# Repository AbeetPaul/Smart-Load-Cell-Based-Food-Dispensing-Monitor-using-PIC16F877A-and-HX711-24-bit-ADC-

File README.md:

# Smart Food Dispensing Monitor: PIC16F877A + HX711

A custom KiCad-designed PCB for precise weight measurement in food dispensing management. The board pairs a PIC16F877A microcontroller with the HX711 24-bit ADC to acquire load cell data using assembly firmware.

## Repository Structure

```
/fabrication    → Primary manufacturing files (e.g., 1st.kicad_sch)
/documentation  → High-resolution PCB layouts and circuit schematics
/firmware       → Assembly source (.asm) and compiled .HEX file
```

## Hardware Architecture

The system combines the versatile PIC family with the 24-bit precision needed for sensitive load cell data acquisition, a balanced and cost-effective solution.

| Component | Specification | Role |
|-----------|---------------|------|
| U1 | PIC16F877A-IP | Central processing unit; runs the assembly logic and manages data flow |
| U2 | HX711 | 24-bit ADC designed for load cell and bridge sensor interfacing |
| Y1 | 4 MHz Crystal | Primary clock source; gives a 1 µs instruction cycle (Fosc/4) |
| R1 | 10k Resistor | Pull-up on MCLR (Pin 1) to prevent accidental resets |
| C1, C2 | 22 pF Capacitors | Stabilize the crystal oscillator for clean clock generation |

### Pin Connections

| PIC16F877A | HX711 | Configuration |
|------------|-------|---------------|
| RB0 (Pin 33) | DOUT (Pin 12) | Input: detects data-ready and receives the serial bitstream |
| RB1 (Pin 34) | PD_SCK (Pin 11) | Output: drives the serial clock and power-down control |

## Firmware Logic

The firmware follows a four-stage communication protocol:

1. **Data-ready polling:** monitors the HX711 using `BTFSC` on `PORTB,0` and waits for DOUT to go low, signaling a completed conversion.
2. **24-bit retrieval:** performs three successive 8-bit reads into `DATA_H` (high), `DATA_M` (middle), and `DATA_L` (low) to rebuild the full 24-bit raw value.
3. **Gain selection:** after the 24th bit, applies a 25th clock pulse by toggling RB1 high then low, setting gain to 128 on Channel A for the next conversion.
4. **Output mapping:** sends `DATA_L` to PORTC (Pins 15-18 and 23-26) for external monitoring, debugging, or immediate processing.

### Timing Note

The 4 MHz oscillator gives a standard 1 µs instruction cycle. The current `DELAY_500MS` loop constants (200 and 250) produce an actual delay of about **250 ms**. If you need a strict 500 ms update rate, adjust these constants.

## Simulation and Deployment

The schematic and PCB layout were developed in KiCad EDA. Verifying the firmware in simulation before building hardware reduces the risk of failure.

### Virtual Simulation
1. Open Proteus or SimulIDE.
2. Load the compiled `.HEX` file from `/firmware` into the virtual PIC16F877A.
3. Monitor the bit-banging sequence on RB0 and RB1 to verify the communication logic and the gain selection pulse.

### Physical Programming
The PCB includes an **ICSP header (J1)**, so the PIC16F877A can be flashed directly on the board. This allows quick firmware updates and final calibration without removing the chip.

## Tech Stack

`PIC16F877A` · `HX711` · `KiCad` · `PIC Assembly` · `Proteus / SimulIDE`

# MindMap

# Final PCB Design

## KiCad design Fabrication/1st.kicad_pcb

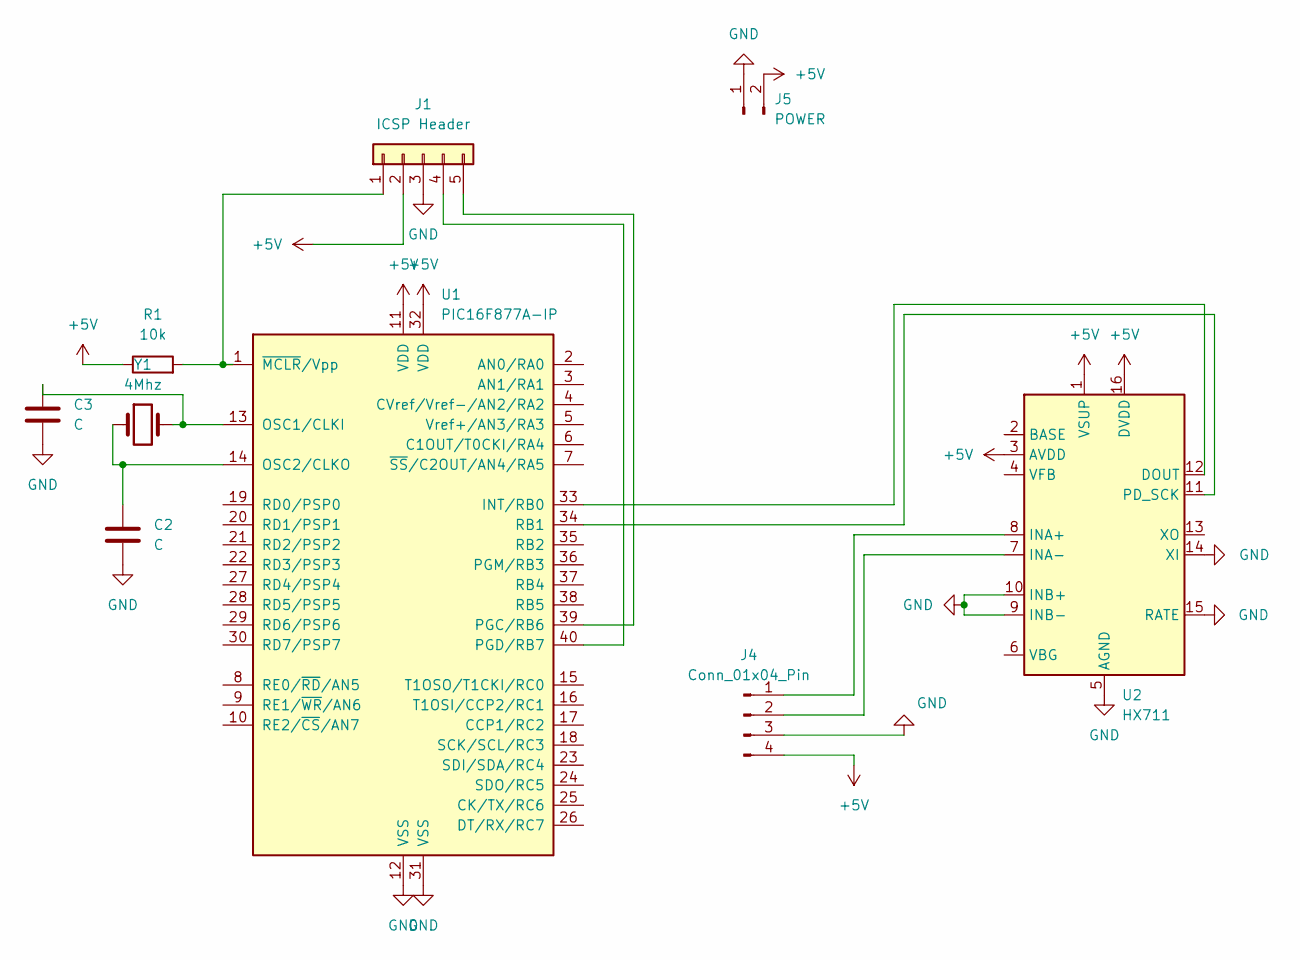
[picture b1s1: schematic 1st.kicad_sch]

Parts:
C2, C3: C; C_Disc_D5.0mm_W2.5mm_P5.00mm
J1: ICSP Header; PinHeader_1x05_P2.54mm_Vertical
J4: Conn_01x04_Pin; PinHeader_1x04_P2.54mm_Vertical
J5: POWER; PinHeader_1x02_P2.54mm_Vertical
R1: 10k; R_Axial_DIN0207_L6.3mm_D2.5mm_P10.16mm_Horizontal
U1: PIC16F877A-IP; DIP-40_W15.24mm
U2: HX711; SOIC-16_3.9x9.9mm_P1.27mm
Y1: 4Mhz; Crystal_HC49-U_Vertical

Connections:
+5V: J1.2, J4.4 (+5V), J5.2, R1.1, U1.11 (VDD), U1.32 (VDD), U2.1 (VSUP), U2.3 (AVDD), U2.16 (DVDD)
GND: C2.2, C3.2, J1.3, J4.3 (GND), J5.1, U1.12 (VSS), U1.31 (VSS), U2.5 (AGND), U2.9 (INB-), U2.10 (INB+), U2.14 (XI), U2.15 (RATE)
unnamed: J1.1, R1.2, U1.1 (~MCLR/Vpp)
unnamed: J1.4, U1.40 (PGD/RB7)
unnamed: J1.5, U1.39 (PGC/RB6)
unnamed: J4.1 (A+), U2.8 (INA+)
unnamed: J4.2 (A-), U2.7 (INA-)
unnamed: U1.33 (INT/RB0), U2.12 (DOUT)
unnamed: C3.1, U1.13 (OSC1/CLKI), Y1.2
unnamed: C2.1, U1.14 (OSC2/CLKO), Y1.1
unnamed: U1.34 (RB1), U2.11 (PD_SCK)

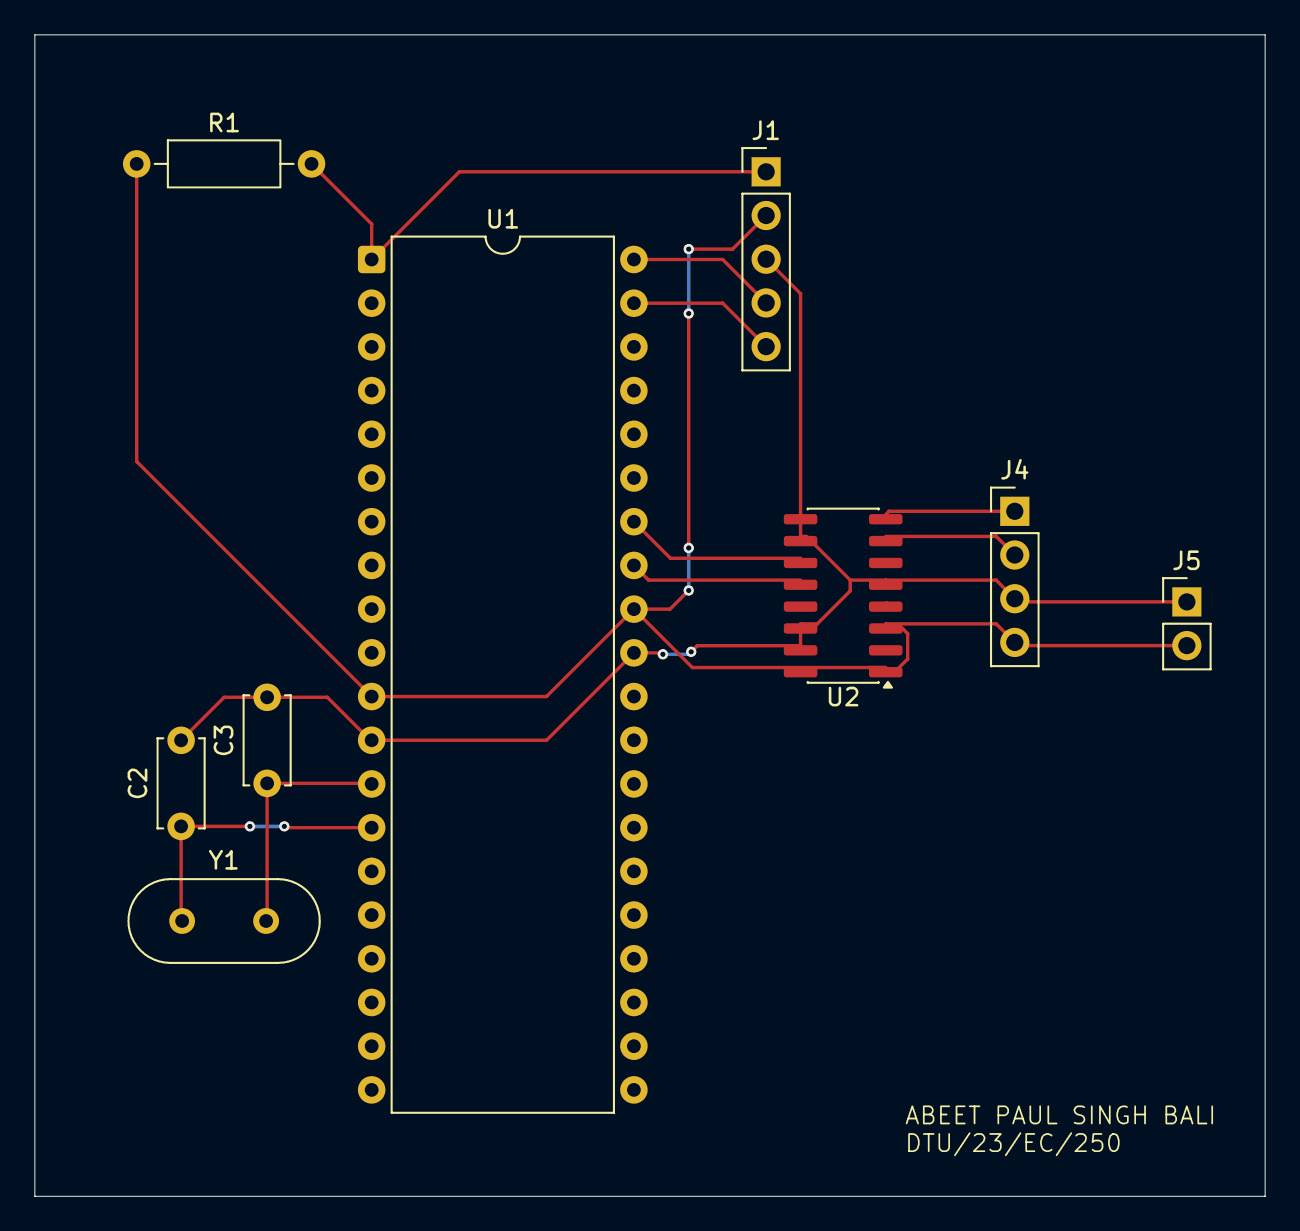
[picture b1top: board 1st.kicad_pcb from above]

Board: 2 copper layers, 71.5 x 67.5 mm, 9 parts (0 on the bottom side), 11 nets.
